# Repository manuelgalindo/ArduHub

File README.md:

# ArduHub

HUB USB/Ethernet integrado compatible con Arduino(R)
HUB USB/Ethernet with Arduino(R).

## License

Copyright (c) 2016 Manuel Fernando Galindo

Design conceded under CERN OHL License.

CERN Open Hardware Licence v1.2 

Preamble

Through this CERN Open Hardware Licence ("CERN OHL") version 1.2, CERN
wishes to provide a tool to foster collaboration and sharing among
hardware designers.  The CERN OHL is copyright CERN. Anyone is welcome
to use the CERN OHL, in unmodified form only, for the distribution of
their own Open Hardware designs. Any other right is reserved. Release
of hardware designs under the CERN OHL does not constitute an
endorsement of the licensor or its designs nor does it imply any
involvement by CERN in the development of such designs.

1. Definitions

In this Licence, the following terms have the following meanings:
 
“Licence” means this CERN OHL.

“Documentation” means schematic diagrams, designs, circuit or circuit
board layouts, mechanical drawings, flow charts and descriptive text,
and other explanatory material that is explicitly stated as being made
available under the conditions of this Licence. The Documentation may
be in any medium, including but not limited to computer files and
representations on paper, film, or any other media.

“Documentation Location” means a location where the Licensor has
placed Documentation, and which he believes will be publicly
accessible for at least three years from the first communication to
the public or distribution of Documentation.

“Product” means either an entire, or any part of a, device built using
the Documentation or the modified Documentation.

“Licensee” means any natural or legal person exercising rights under
this Licence.

“Licensor” means any natural or legal person that creates or modifies
Documentation and subsequently communicates to the public and/ or
distributes the resulting Documentation under the terms and conditions
of this Licence.

A Licensee may at the same time be a Licensor, and vice versa. 

Use of the masculine gender includes the feminine and neuter genders
and is employed solely to facilitate reading.

2. Applicability

2.1. This Licence governs the use, copying, modification,
communication to the public and distribution of the Documentation, and
the manufacture and distribution of Products. By exercising any right
granted under this Licence, the Licensee irrevocably accepts these
terms and conditions.

2.2. This Licence is granted by the Licensor directly to the Licensee,
and shall apply worldwide and without limitation in time. The Licensee
may assign his licence rights or grant sub-licences.

2.3. This Licence does not extend to software, firmware, or code
loaded into programmable devices which may be used in conjunction with
the Documentation, the modified Documentation or with Products, unless
such software, firmware, or code is explicitly expressed to be subject
to this Licence. The use of such software, firmware, or code is
otherwise subject to the applicable licence terms and conditions.

3. Copying, modification, communication to the public and distribution
of the Documentation

3.1. The Licensee shall keep intact all copyright and trademarks
notices, all notices referring to Documentation Location, and all
notices that refer to this Licence and to the disclaimer of warranties
that are included in the Documentation. He shall include a copy
thereof in every copy of the Documentation or, as the case may be,
modified Documentation, that he communicates to the public or
distributes.

3.2. The Licensee may copy, communicate to the public and distribute
verbatim copies of the Documentation, in any medium, subject to the
requirements specified in section 3.1.

3.3. The Licensee may modify the Documentation or any portion thereof
provided that upon modification of the Documentation, the Licensee
shall make the modified Documentation available from a Documentation
Location such that it can be easily located by an original Licensor
once the Licensee communicates to the public or distributes the
modified Documentation under section 3.4, and, where required by
section 4.1, by a recipient of a Product. However, the Licensor shall
not assert his rights under the foregoing proviso unless or until a
Product is distributed.

3.4. The Licensee may communicate to the public and distribute the
modified Documentation (thereby in addition to being a Licensee also
becoming a Licensor), always provided that he shall:

a) comply with section 3.1;

b) cause the modified Documentation to carry prominent notices stating
that the Licensee has modified the Documentation, with the date and
description of the modifications;

c) cause the modified Documentation to carry a new Documentation
Location notice if the original Documentation provided for one;

d) make available the modified Documentation at the same level of
abstraction as that of the Documentation, in the preferred format for
making modifications to it (e.g. the native format of the CAD tool as
applicable), and in the event that format is proprietary, in a format
viewable with a tool licensed under an OSI-approved license if the
proprietary tool can create it; and

e) license the modified Documentation under the terms and conditions
of this Licence or, where applicable, a later version of this Licence
as may be issued by CERN.

3.5. The Licence includes a non-exclusive licence to those patents or
registered designs that are held by, under the control of, or
sub-licensable by the Licensor, to the extent necessary to make use of
the rights granted under this Licence. The scope of this section 3.5
shall be strictly limited to the parts of the Documentation or
modified Documentation created by the Licensor.

4. Manufacture and distribution of Products

4.1. The Licensee may manufacture or distribute Products always
provided that, where such manufacture or distribution requires a
licence under this Licence the Licensee provides to each recipient of
such Products an easy means of accessing a copy of the Documentation
or modified Documentation, as applicable, as set out in section 3.

4.2. The Licensee is invited to inform any Licensor who has indicated
his wish to receive this information about the type, quantity and
dates of production of Products the Licensee has (had) manufactured

5. Warranty and liability

5.1. DISCLAIMER – The Documentation and any modified Documentation are
provided "as is" and any express or implied warranties, including, but
not limited to, implied warranties of merchantability, of satisfactory
quality, non-infringement of third party rights, and fitness for a
particular purpose or use are disclaimed in respect of the
Documentation, the modified Documentation or any Product. The Licensor
makes no representation that the Documentation, modified
Documentation, or any Product, does or will not infringe any patent,
copyright, trade secret or other proprietary right. The entire risk as
to the use, quality, and performance of a Product shall be with the
Licensee and not the Licensor. This disclaimer of warranty is an
essential part of this Licence and a condition for the grant of any
rights granted under this Licence. The Licensee warrants that it does
not act in a consumer capacity.

5.2. LIMITATION OF LIABILITY – The Licensor shall have no liability
for direct, indirect, special, incidental, consequential, exemplary,
punitive or other damages of any character including, without
limitation, procurement of substitute goods or services, loss of use,
data or profits, or business interruption, however caused and on any
theory of contract, warranty, tort (including negligence), product
liability or otherwise, arising in any way in relation to the
Documentation, modified Documentation and/or the use, manufacture or
distribution of a Product, even if advised of the possibility of such
damages, and the Licensee shall hold the Licensor(s) free and harmless
from any liability, costs, damages, fees and expenses, including
claims by third parties, in relation to such use.

6. General

6.1. Except for the rights explicitly granted hereunder, this Licence
does not imply or represent any transfer or assignment of intellectual
property rights to the Licensee.

6.2. The Licensee shall not use or make reference to any of the names
(including acronyms and abbreviations), images, or logos under which
the Licensor is known, save in so far as required to comply with
section 3. Any such permitted use or reference shall be factual and
shall in no event suggest any kind of endorsement by the Licensor or
its personnel of the modified Documentation or any Product, or any
kind of implication by the Licensor or its personnel in the
preparation of the modified Documentation or Product.

6.3. CERN may publish updated versions of this Licence which retain
the same general provisions as this version, but differ in detail so
far this is required and reasonable. New versions will be published
with a unique version number.

6.4. This Licence shall terminate with immediate effect, upon written
notice and without involvement of a court if the Licensee fails to
comply with any of its terms and conditions, or if the Licensee
initiates legal action against Licensor in relation to this
Licence. Section 5 shall continue to apply.

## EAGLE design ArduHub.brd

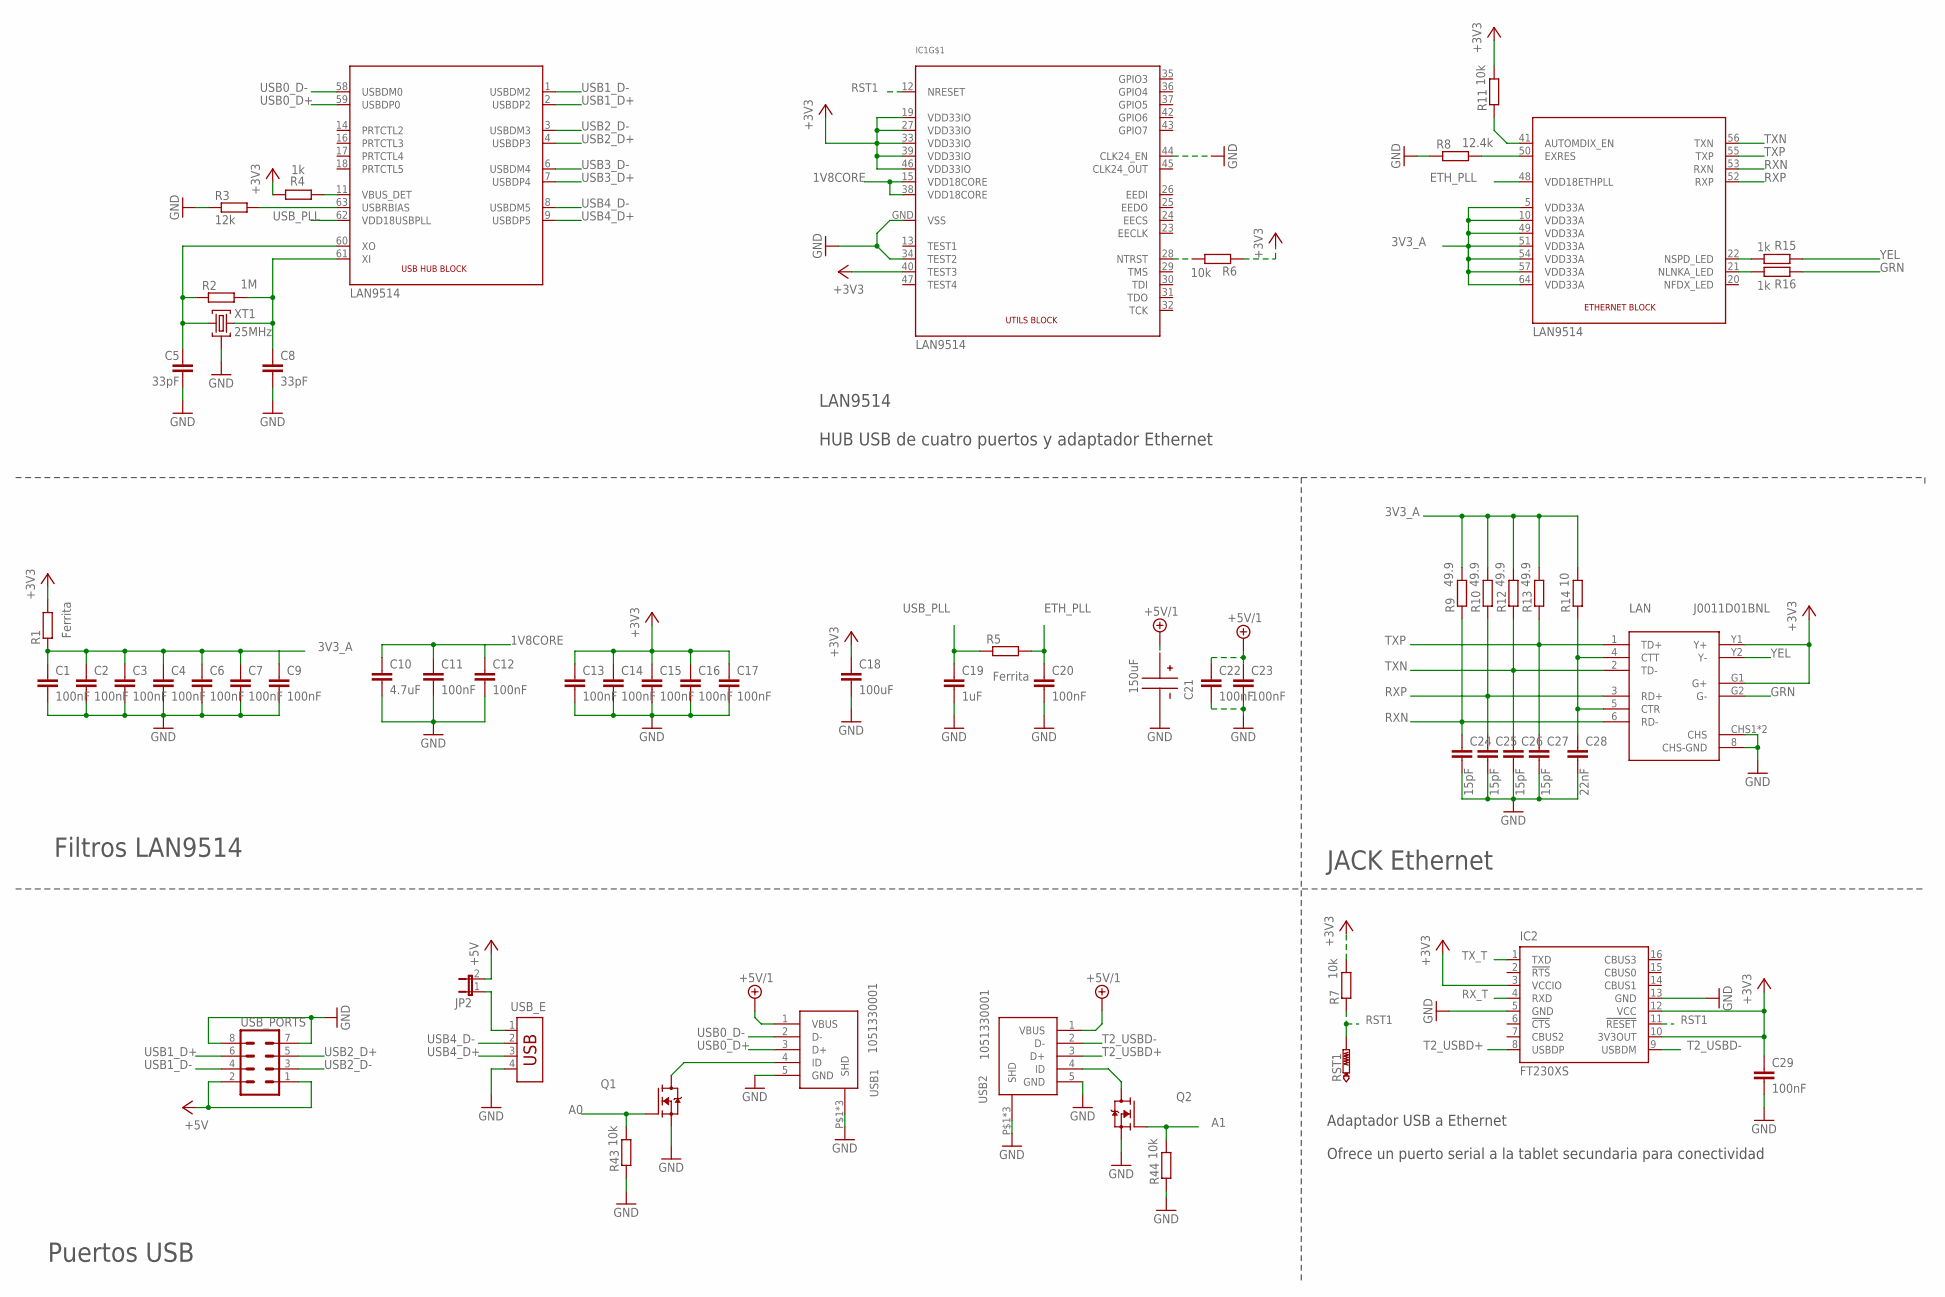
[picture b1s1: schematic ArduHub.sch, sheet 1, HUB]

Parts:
C1, C2, C3, C4, C6, C7, C9, C11, C12, C13, C14, C15, C16, C17, C20, C22, C23, C29: 100nF; C0402
C5, C8: 33pF; C0402
C10: 4.7uF; C0402
C18: 100uF; C0603
C19: 1uF; C0402
C21: 150uF; MVA_CAP_F55
C24, C25, C26, C27: 15pF; C0402
C28: 22nF; C0402
IC1: LAN9514; QFN64
IC2: FT230XS; SSOP16
JP2: JP1E; JP1
LAN: J0011D01BNL
Q1, Q2: TRANSISTOR_FET_BS170-SOT-23; SOT-23
R1, R5: Ferrita; R0603
R2: 1M; R0402
R3: 12k; R0402
R4, R15, R16: 1k; R0402
R6, R7, R11, R43, R44: 10k; R0402
R8: 12.4k; R0402
R9, R10, R12, R13: 49.9; R0402
R14: 10; R0402
RST1: PTR1B1,27; B1,27
USB1, USB2: 1051330001
USB_E: USB-787616; USB
USB_PORTS: MA04-2
XT1: 25MHz; ABM8G

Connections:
1V8CORE: C10.1, C11.1, C12.1, IC1.15 (VDD18CORE), IC1.38 (VDD18CORE)
3V3_A: C1.1, C2.1, C3.1, C4.1, C6.1, C7.1, C9.1, IC1.5 (VDD33A), IC1.10 (VDD33A), IC1.49 (VDD33A), IC1.51 (VDD33A), IC1.54 (VDD33A), IC1.57 (VDD33A), IC1.64 (VDD33A), R1.1, R9.2, R10.2, R12.2, R13.2, R14.2
+3V3: C13.1, C14.1, C15.1, C16.1, C17.1, C18.1, C29.1, IC1.19 (VDD33IO), IC1.27 (VDD33IO), IC1.33 (VDD33IO), IC1.39 (VDD33IO), IC1.40 (TEST3), IC1.46 (VDD33IO), IC2.3 (VCCIO), IC2.10 (3V3OUT), IC2.12 (VCC), LAN.G1 (G+), LAN.Y1 (Y+), R1.2, R4.2, R6.1, R7.2, R11.2; also elsewhere on the board
+5V: JP2.2, USB_PORTS.1, USB_PORTS.2; also elsewhere on the board
+5V/1: C21.P$+, C22.1, C23.1, USB1.1 (VBUS), USB2.1 (VBUS); also elsewhere on the board
A0: Q1.1 (G), R43.2; also elsewhere on the board
A1: Q2.1 (G), R44.2; also elsewhere on the board
ETH_PLL: C20.1, IC1.48 (VDD18ETHPLL), R5.2
GND: C1.2, C2.2, C3.2, C4.2, C5.2, C6.2, C7.2, C8.2, C9.2, C10.2, C11.2, C12.2, C13.2, C14.2, C15.2, C16.2, C17.2, C18.2, C19.2, C20.2, C21.P$-, C22.2, C23.2, C24.2, C25.2, C26.2, C27.2, C28.2, C29.2, IC1.34 (TEST2), IC1.44 (CLK24_EN), IC1.GND (VSS), IC2.5 (GND), IC2.13 (GND), LAN.8 (CHS-GND), LAN.CHS1 (CHS), LAN.CHS2 (CHS), Q1.2 (S), Q2.2 (S), R3.1, R8.1, R43.1, R44.1, USB1.5 (GND), USB1.P$1 (SHD), USB1.P$2 (SHD), USB1.P$3 (SHD), USB2.5 (GND), USB2.P$1 (SHD), USB2.P$2 (SHD), USB2.P$3 (SHD), USB_E.4, USB_PORTS.7, USB_PORTS.8, XT1.2, XT1.4 (2); also elsewhere on the board
GRN: LAN.G2 (G-), R16.1
unnamed: C5.1, IC1.60 (XO), R2.1, XT1.1
unnamed: C8.1, IC1.61 (XI), R2.2, XT1.3
unnamed: IC1.50 (EXRES), R8.2
unnamed: IC1.63 (USBRBIAS), R3.2
unnamed: C28.1, LAN.4 (CTT), LAN.5 (CTR), R14.1
unnamed: IC1.41 (AUTOMDIX_EN), R11.1
unnamed: IC1.21 (NLNKA_LED), R16.2
unnamed: IC1.22 (NSPD_LED), R15.2
unnamed: Q1.3 (D), USB1.4 (ID)
unnamed: IC1.28 (NTRST), R6.2
unnamed: Q2.3 (D), USB2.4 (ID)
unnamed: IC1.11 (VBUS_DET), R4.1
unnamed: JP2.1, USB_E.1
RST1: IC1.12 (NRESET), IC2.11 (!RESET), R7.1, RST1.TP; also elsewhere on the board
RXN: C24.1, IC1.53 (RXN), LAN.6 (RD-), R9.1
RXP: C25.1, IC1.52 (RXP), LAN.3 (RD+), R10.1
RX_T: IC2.4 (RXD); also elsewhere on the board
T2_USBD+: IC2.8 (USBDP), USB2.3 (D+)
T2_USBD-: IC2.9 (USBDM), USB2.2 (D-)
TXN: C26.1, IC1.56 (TXN), LAN.2 (TD-), R12.1
TXP: C27.1, IC1.55 (TXP), LAN.1 (TD+), R13.1
TX_T: IC2.1 (TXD); also elsewhere on the board
USB0_D+: IC1.59 (USBDP0), USB1.3 (D+)
USB0_D-: IC1.58 (USBDM0), USB1.2 (D-)
USB1_D+: IC1.2 (USBDP2), USB_PORTS.6
USB1_D-: IC1.1 (USBDM2), USB_PORTS.4
USB2_D+: IC1.4 (USBDP3), USB_PORTS.5
USB2_D-: IC1.3 (USBDM3), USB_PORTS.3
USB3_D+: IC1.7 (USBDP4); also elsewhere on the board
USB3_D-: IC1.6 (USBDM4); also elsewhere on the board
USB4_D+: IC1.9 (USBDP5), USB_E.3
USB4_D-: IC1.8 (USBDM5), USB_E.2
USB_PLL: C19.1, IC1.62 (VDD18USBPLL), R5.1
YEL: LAN.Y2 (Y-), R15.1

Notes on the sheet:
LAN9514 HUB USB de cuatro puertos y adaptador Ethernet
Filtros LAN9514
JACK Ethernet
Adaptador USB a Ethernet Ofrece un puerto serial a la tablet secundaria para conectividad
Puertos USB

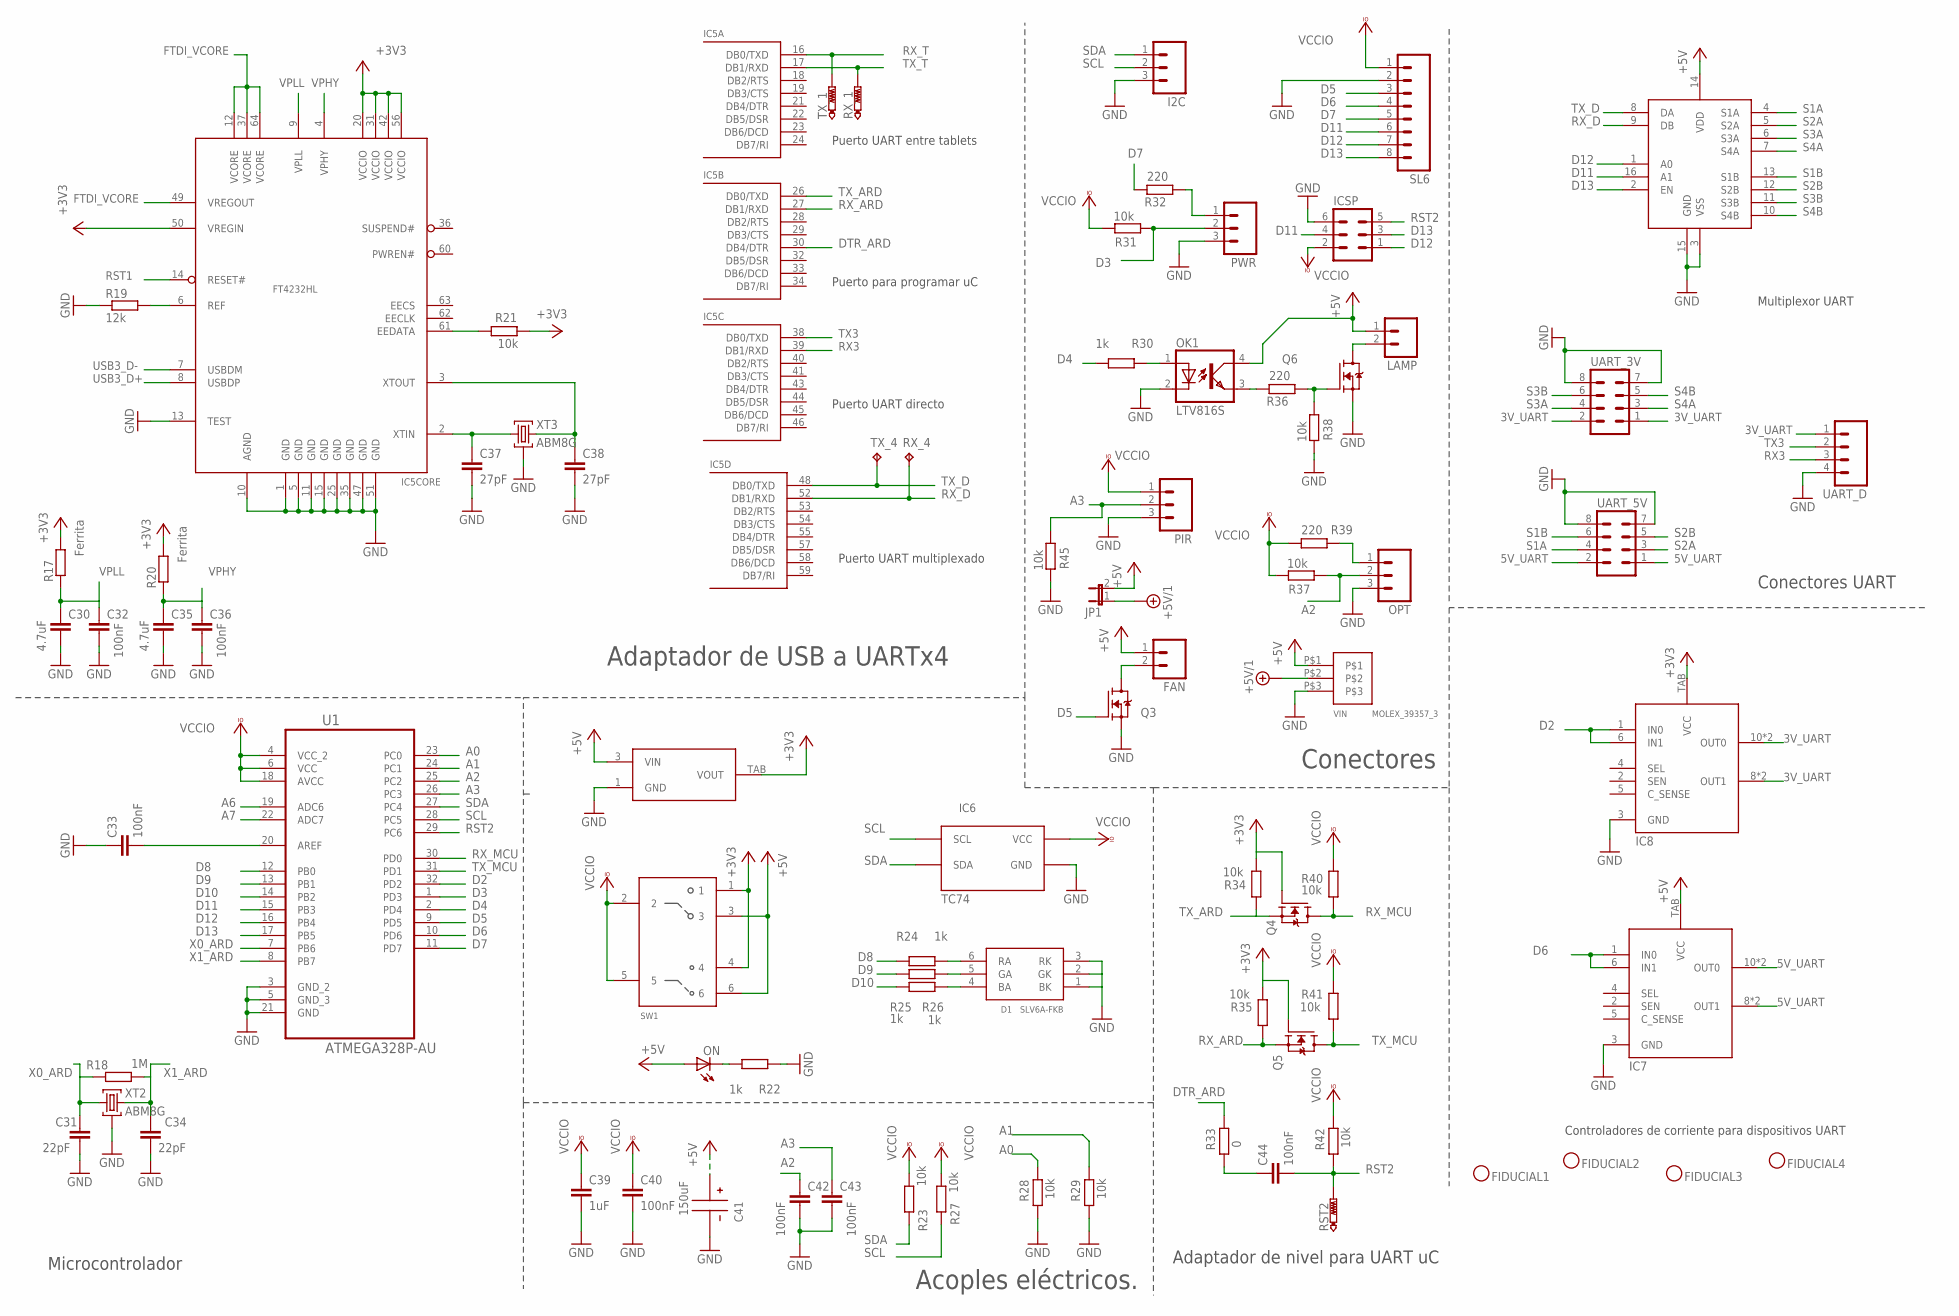
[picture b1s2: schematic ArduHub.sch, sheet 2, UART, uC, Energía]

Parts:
C30, C35: 4.7uF; C0402
C31, C34: 22pF; C0402
C32, C33, C36, C40, C42, C43, C44: 100nF; C0402
C37, C38: 27pF; C0402
C39: 1uF; C0402
C41: 150uF; MVA_CAP_F55
D1: SLV6A-FKB; PLCC-6
FAN: M02; 02P
FIDUCIAL1, FIDUCIAL2, FIDUCIAL3, FIDUCIAL4: FIDU_2C; FIDUCIAL_TEST_2C
I2C: M03; 03P
IC4: AP1084D; TO_252_3
IC5: FT4232HL; LQFP64
IC6: TC74; SOT-23-5
IC7, IC8: VND7140AJ12TR; POWERSSO-12
IC9: MUX509IPWR; TSSOP-16
ICSP: MA03-2
JP1: JP1E; JP1
LAMP: M02; 02P
OK1: LTV816S; SMD4
ON: LED-0603; LED-603
OPT: M03; 03P
PIR: M03; 03P
PWR: M03; 03P
Q3, Q4, Q5, Q6: TRANSISTOR_FET_BS170-SOT-23; SOT-23
R17, R20: Ferrita; R0603
R18: 1M; R0402
R19: 12k; R0402
R21, R23, R27, R28, R29, R31, R34, R35, R37, R38, R40, R41, R42, R45: 10k; R0402
R22, R24, R25, R26, R30: 1k; R0402
R32, R36, R39: 220; R0402
R33: 0; R0402
RST2: PTR1TP06SQ; TP06SQ
RX_1: PTR1TP06SQ; TP06SQ
RX_4: TPTP06SQ; TP06SQ
SL6: M08; 08P
SW1: 452403012014
TX_1: PTR1TP06SQ; TP06SQ
TX_4: TPTP06SQ; TP06SQ
U1: ATMEGA328P-AU; QFP80P900X900X120-32N
UART_3V, UART_5V: MA04-2
UART_D: M04; 04P
VIN: MOLEX_39357_3; MOLEX_39357-3
XT2, XT3: ABM8G

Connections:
3V_UART: IC8.8 (OUT1), IC8.9 (OUT1), IC8.10 (OUT0), IC8.11 (OUT0), UART_3V.1, UART_3V.2, UART_D.1
5V_UART: IC7.8 (OUT1), IC7.9 (OUT1), IC7.10 (OUT0), IC7.11 (OUT0), UART_5V.1, UART_5V.2
+3V3: IC4.TAB (VOUT), IC5.20 (VCCIO), IC5.31 (VCCIO), IC5.42 (VCCIO), IC5.50 (VREGIN), IC5.56 (VCCIO), IC8.TAB (VCC), Q4.1 (G), Q5.1 (G), R17.2, R20.2, R21.1, R34.1, R35.1, SW1.1, SW1.4; also elsewhere on the board
+5V: C41.P$+, FAN.1, IC4.3 (VIN), IC7.TAB (VCC), IC9.14 (VDD), JP1.2, LAMP.1, OK1.4 (COL), ON.A, SW1.3, SW1.6, VIN.P$1; also elsewhere on the board
+5V/1: JP1.1, VIN.P$2; also elsewhere on the board
A0: R28.1, U1.23 (PC0); also elsewhere on the board
A1: R29.1, U1.24 (PC1); also elsewhere on the board
A2: C42.1, OPT.2, R37.2, U1.25 (PC2)
A3: C43.1, PIR.2, R45.2, U1.26 (PC3)
A6: U1.19 (ADC6)
A7: U1.22 (ADC7)
D2: IC8.1 (IN0), IC8.6 (IN1), U1.32 (PD2)
D3: PWR.2, R31.2, U1.1 (PD3)
D4: R30.2, U1.2 (PD4)
D5: Q3.1 (G), SL6.3, U1.9 (PD5)
D6: IC7.1 (IN0), IC7.6 (IN1), SL6.4, U1.10 (PD6)
D7: R32.2, SL6.5, U1.11 (PD7)
D8: R24.1, U1.12 (PB0)
D9: R25.1, U1.13 (PB1)
D10: R26.1, U1.14 (PB2)
D11: IC9.16 (A1), ICSP.4, SL6.6, U1.15 (PB3)
D12: IC9.1 (A0), ICSP.1, SL6.7, U1.16 (PB4)
D13: IC9.2 (EN), ICSP.3, SL6.8, U1.17 (PB5)
DTR_ARD: IC5.30 (DB4/DTR), R33.1
FTDI_VCORE: IC5.12 (VCORE), IC5.37 (VCORE), IC5.49 (VREGOUT), IC5.64 (VCORE)
GND: C30.2, C31.2, C32.2, C33.1, C34.2, C35.2, C36.2, C37.2, C38.2, C39.2, C40.2, C41.P$-, C42.2, C43.2, D1.1 (BK), D1.2 (GK), D1.3 (RK), I2C.3, IC4.1 (GND), IC5.1 (GND), IC5.5 (GND), IC5.10 (AGND), IC5.11 (GND), IC5.13 (TEST), IC5.15 (GND), IC5.25 (GND), IC5.35 (GND), IC5.47 (GND), IC5.51 (GND), IC6.2 (GND), IC7.3 (GND), IC8.3 (GND), IC9.3 (VSS), IC9.15 (GND), ICSP.6, OK1.2 (C), OPT.3, PIR.3, PWR.3, Q3.2 (S), Q6.2 (S), R19.1, R22.1, R28.2, R29.2, R38.1, R45.1, SL6.2, U1.3 (GND_2), U1.5 (GND_3), U1.21 (GND), UART_3V.7, UART_3V.8, UART_5V.7, UART_5V.8, UART_D.4, VIN.P$3, XT2.2, XT2.4 (2), XT3.2, XT3.4 (2); also elsewhere on the board
unnamed: IC5.61 (EEDATA), R21.2
unnamed: IC5.6 (REF), R19.2
unnamed: C37.1, IC5.2 (XTIN), XT3.1
unnamed: C38.1, IC5.3 (XTOUT), XT3.3
unnamed: C33.2, U1.20 (AREF)
unnamed: D1.6 (RA), R24.2
unnamed: D1.5 (GA), R25.2
unnamed: D1.4 (BA), R26.2
unnamed: ON.C, R22.2
unnamed: LAMP.2, Q6.3 (D)
unnamed: OPT.1, R39.1
unnamed: Q6.1 (G), R36.1, R38.2
unnamed: OK1.3 (EMIT), R36.2
unnamed: OK1.1 (A), R30.1
unnamed: FAN.2, Q3.3 (D)
unnamed: PWR.1, R32.1
unnamed: C44.1, R33.2
RST1: IC5.14 (RESET#); also elsewhere on the board
RST2: C44.2, ICSP.5, R42.2, RST2.TP, U1.29 (PC6)
RX3: IC5.39 (DB1/RXD), UART_D.3
RX_ARD: IC5.27 (DB1/RXD), Q5.2 (S), R35.2
RX_D: IC5.52 (DB1/RXD), IC9.9 (DB), RX_4.TP
RX_MCU: Q4.3 (D), R40.2, U1.30 (PD0)
RX_T: IC5.16 (DB0/TXD), TX_1.TP; also elsewhere on the board
S1A: IC9.4 (S1A), UART_5V.4
S1B: IC9.13 (S1B), UART_5V.6
S2A: IC9.5 (S2A), UART_5V.3
S2B: IC9.12 (S2B), UART_5V.5
S3A: IC9.6 (S3A), UART_3V.4
S3B: IC9.11 (S3B), UART_3V.6
S4A: IC9.7 (S4A), UART_3V.3
S4B: IC9.10 (S4B), UART_3V.5
SCL: I2C.2, IC6.4 (SCL), R27.2, U1.28 (PC5)
SDA: I2C.1, IC6.5 (SDA), R23.2, U1.27 (PC4)
TX3: IC5.38 (DB0/TXD), UART_D.2
TX_ARD: IC5.26 (DB0/TXD), Q4.2 (S), R34.2
TX_D: IC5.48 (DB0/TXD), IC9.8 (DA), TX_4.TP
TX_MCU: Q5.3 (D), R41.2, U1.31 (PD1)
TX_T: IC5.17 (DB1/RXD), RX_1.TP; also elsewhere on the board
USB3_D+: IC5.8 (USBDP); also elsewhere on the board
USB3_D-: IC5.7 (USBDM); also elsewhere on the board
VCCIO: C39.1, C40.1, IC6.3 (VCC), ICSP.2, PIR.1, R23.1, R27.1, R31.1, R37.1, R39.2, R40.1, R41.1, R42.1, SL6.1, SW1.2, SW1.5, U1.4 (VCC_2), U1.6 (VCC), U1.18 (AVCC)
VPHY: C35.1, C36.1, IC5.4 (VPHY), R20.1
VPLL: C30.1, C32.1, IC5.9 (VPLL), R17.1
X0_ARD: C31.1, R18.1, U1.7 (PB6), XT2.1
X1_ARD: C34.1, R18.2, U1.8 (PB7), XT2.3

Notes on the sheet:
Puerto UART entre tablets
Puerto para programar uC
Puerto UART directo
Puerto UART multiplexado
Multiplexor UART
Controladores de corriente para dispositivos UART
Adaptador de USB a UARTx4
Conectores UART
Microcontrolador
Conectores
Adaptador de nivel para UART uC
Acoples eléctricos.

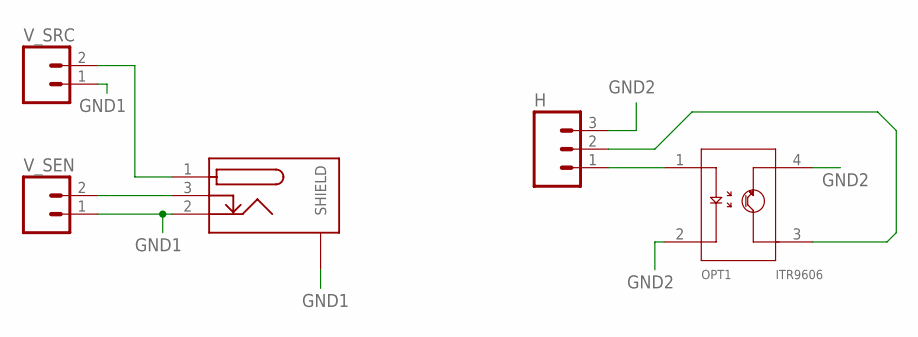
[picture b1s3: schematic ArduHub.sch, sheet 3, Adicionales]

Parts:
H: M03; 03P
OPT1: ITR9606
PLUG: PJ051A
V_SEN: M02; 02P
V_SRC: M02; 02P

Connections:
GND1: PLUG.2, PLUG.P$1 (SHIELD), PLUG.P$2 (SHIELD), V_SEN.1, V_SRC.1
GND2: H.3, OPT1.2, OPT1.4
unnamed: H.1, OPT1.1
unnamed: H.2, OPT1.3
unnamed: PLUG.3, V_SEN.2
unnamed: PLUG.1, V_SRC.2

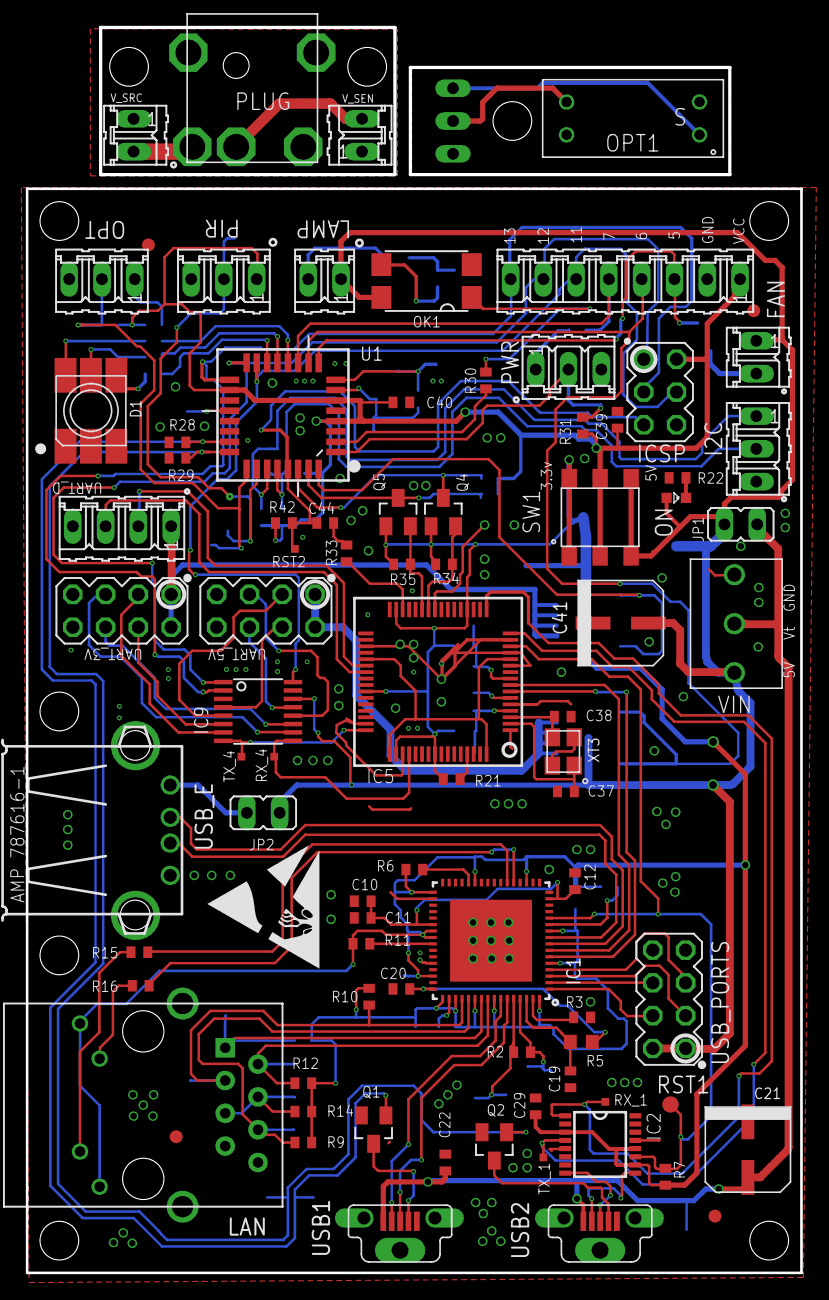
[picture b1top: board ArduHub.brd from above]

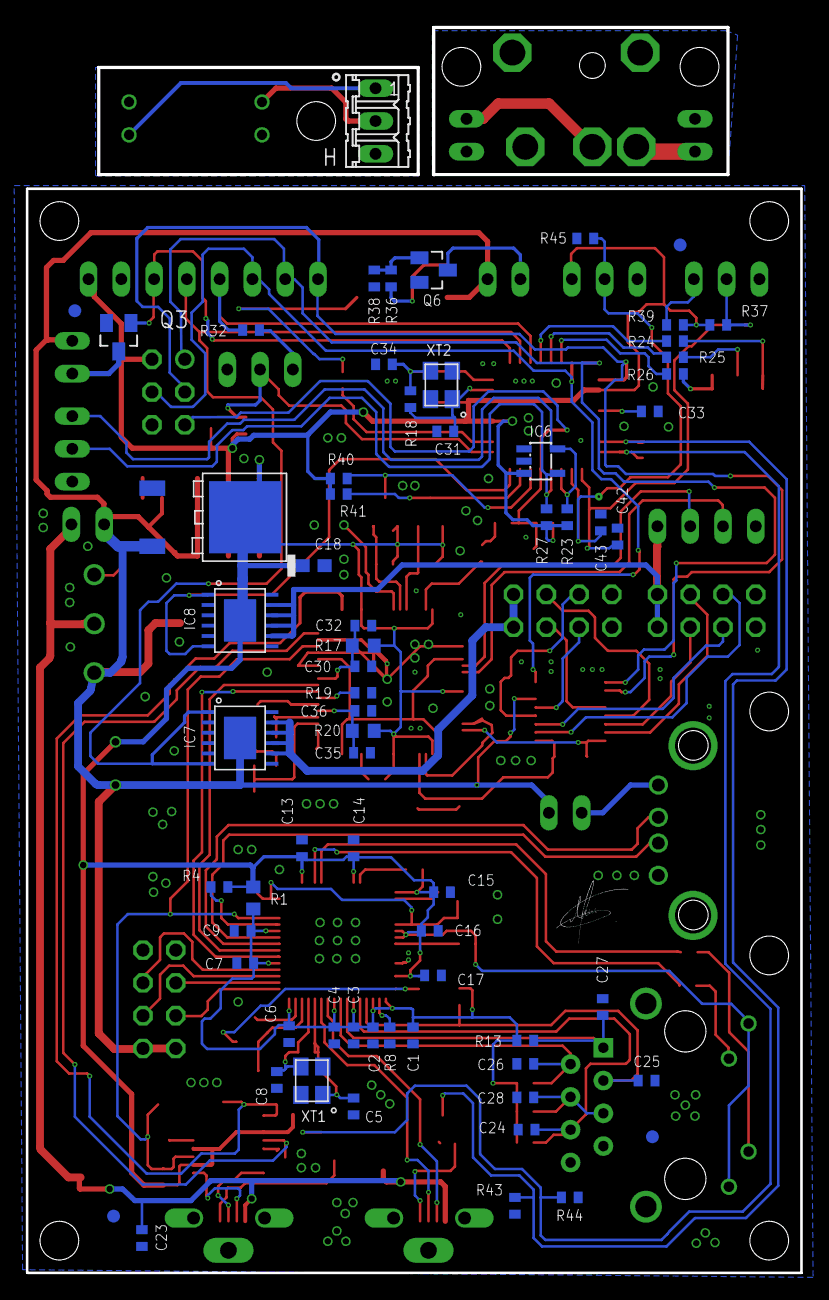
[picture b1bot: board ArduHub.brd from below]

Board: 2 copper layers, 60.0 x 84.0 mm, 147 parts (63 on the bottom side), 109 nets.

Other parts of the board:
U$1: FIRMA
U$3: STATIC

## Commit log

2016-11-12 :tada: Added .gitattributes & .gitignore files
2016-11-12 Stable version
2016-11-12 License
